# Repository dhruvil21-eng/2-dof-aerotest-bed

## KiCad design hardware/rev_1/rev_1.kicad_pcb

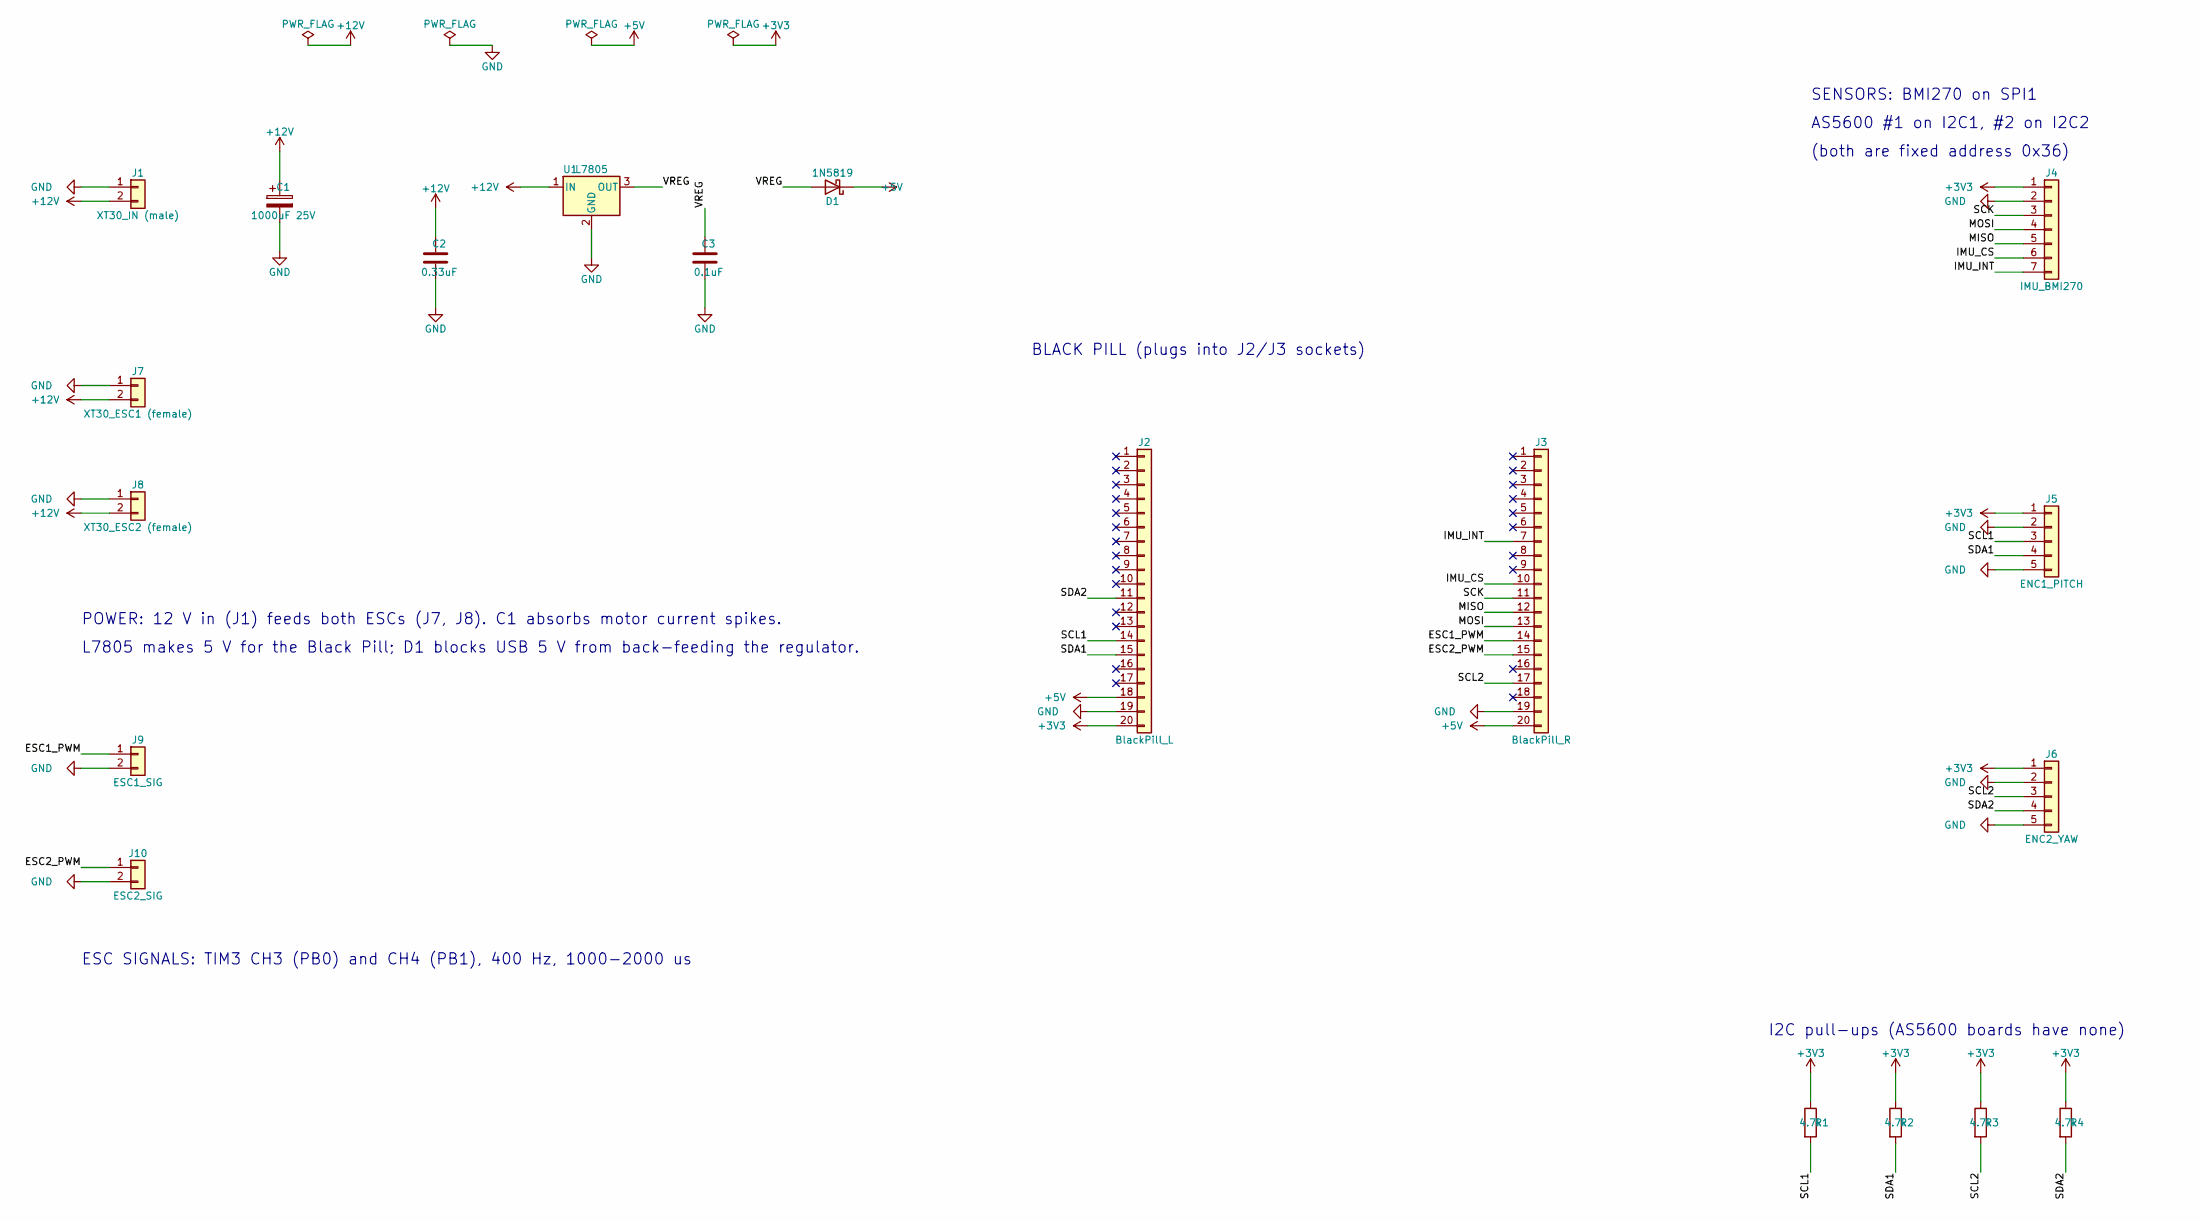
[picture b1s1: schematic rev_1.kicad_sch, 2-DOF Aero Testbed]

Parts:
C1: 1000uF 25V; CP_Radial_D10.0mm_P5.00mm
C2: 0.33uF; C_Disc_D5.0mm_W2.5mm_P5.00mm
C3: 0.1uF; C_Disc_D5.0mm_W2.5mm_P5.00mm
D1: 1N5819; D_DO-41_SOD81_P10.16mm_Horizontal
J1: XT30_IN (male); AMASS_XT30PW-M_1x02_P2.50mm_Horizontal
J2: BlackPill_L; PinSocket_1x20_P2.54mm_Vertical
J3: BlackPill_R; PinSocket_1x20_P2.54mm_Vertical
J4: IMU_BMI270; PinHeader_1x07_P2.54mm_Vertical
J5: ENC1_PITCH; PinHeader_1x05_P2.54mm_Vertical
J6: ENC2_YAW; PinHeader_1x05_P2.54mm_Vertical
J7: XT30_ESC1 (female); AMASS_XT30PW-F_1x02_P2.50mm_Horizontal
J8: XT30_ESC2 (female); AMASS_XT30PW-F_1x02_P2.50mm_Horizontal
J9: ESC1_SIG; PinHeader_1x02_P2.54mm_Vertical
J10: ESC2_SIG; PinHeader_1x02_P2.54mm_Vertical
R1, R2, R3, R4: 4.7k; R_Axial_DIN0207_L6.3mm_D2.5mm_P10.16mm_Horizontal
U1: L7805; TO-220-3_Vertical

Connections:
+3V3: J2.20, J4.1, J5.1, J6.1, R1.1, R2.1, R3.1, R4.1
+5V: D1.1 (K), J2.18, J3.20
+12V: C1.1, C2.1, J1.2, J7.2, J8.2, U1.1 (IN)
ESC1_PWM: J3.14, J9.1
ESC2_PWM: J3.15, J10.1
GND: C1.2, C2.2, C3.2, J1.1, J2.19, J3.19, J4.2, J5.2, J5.5, J6.2, J6.5, J7.1, J8.1, J9.2, J10.2, U1.2 (GND)
IMU_CS: J3.10, J4.6
IMU_INT: J3.7, J4.7
MISO: J3.12, J4.5
MOSI: J3.13, J4.4
SCK: J3.11, J4.3
SCL1: J2.14, J5.3, R1.2
SCL2: J3.17, J6.3, R3.2
SDA1: J2.15, J5.4, R2.2
SDA2: J2.11, J6.4, R4.2
VREG: C3.1, D1.2 (A), U1.3 (OUT)

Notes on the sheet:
BLACK PILL (plugs into J2/J3 sockets)
L7805 makes 5 V for the Black Pill; D1 blocks USB 5 V from back-feeding the regulator.
AS5600 #1 on I2C1, #2 on I2C2
(both are fixed address 0x36)
ESC SIGNALS: TIM3 CH3 (PB0) and CH4 (PB1), 400 Hz, 1000-2000 us
I2C pull-ups (AS5600 boards have none)
SENSORS: BMI270 on SPI1
POWER: 12 V in (J1) feeds both ESCs (J7, J8). C1 absorbs motor current spikes.

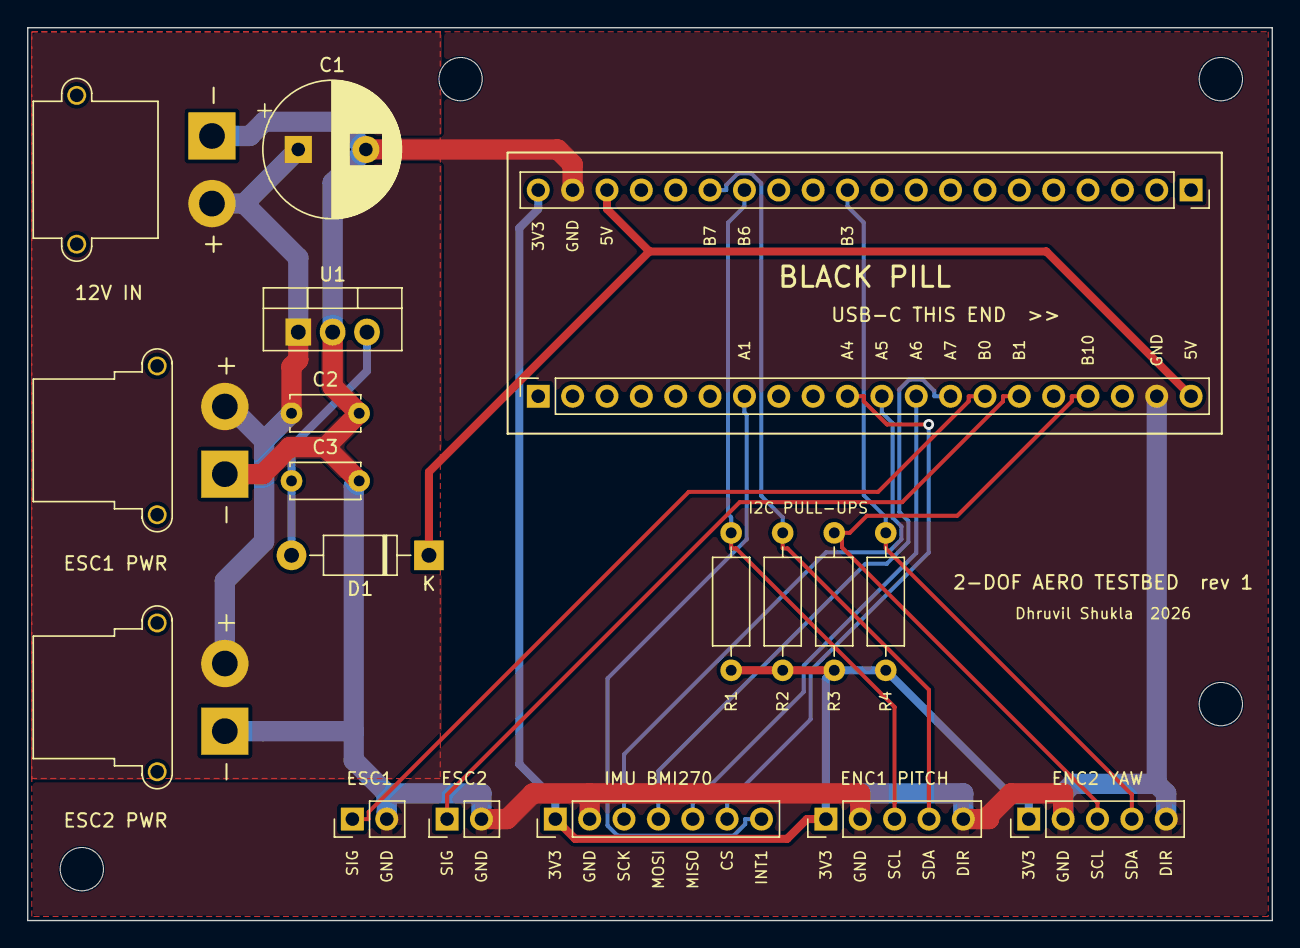
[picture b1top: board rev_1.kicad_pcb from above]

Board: 2 copper layers, 92.0 x 66.0 mm, 23 parts (0 on the bottom side), 16 nets.

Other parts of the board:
H1, H2, H3, H4: MountingHole_3.2mm_M3
